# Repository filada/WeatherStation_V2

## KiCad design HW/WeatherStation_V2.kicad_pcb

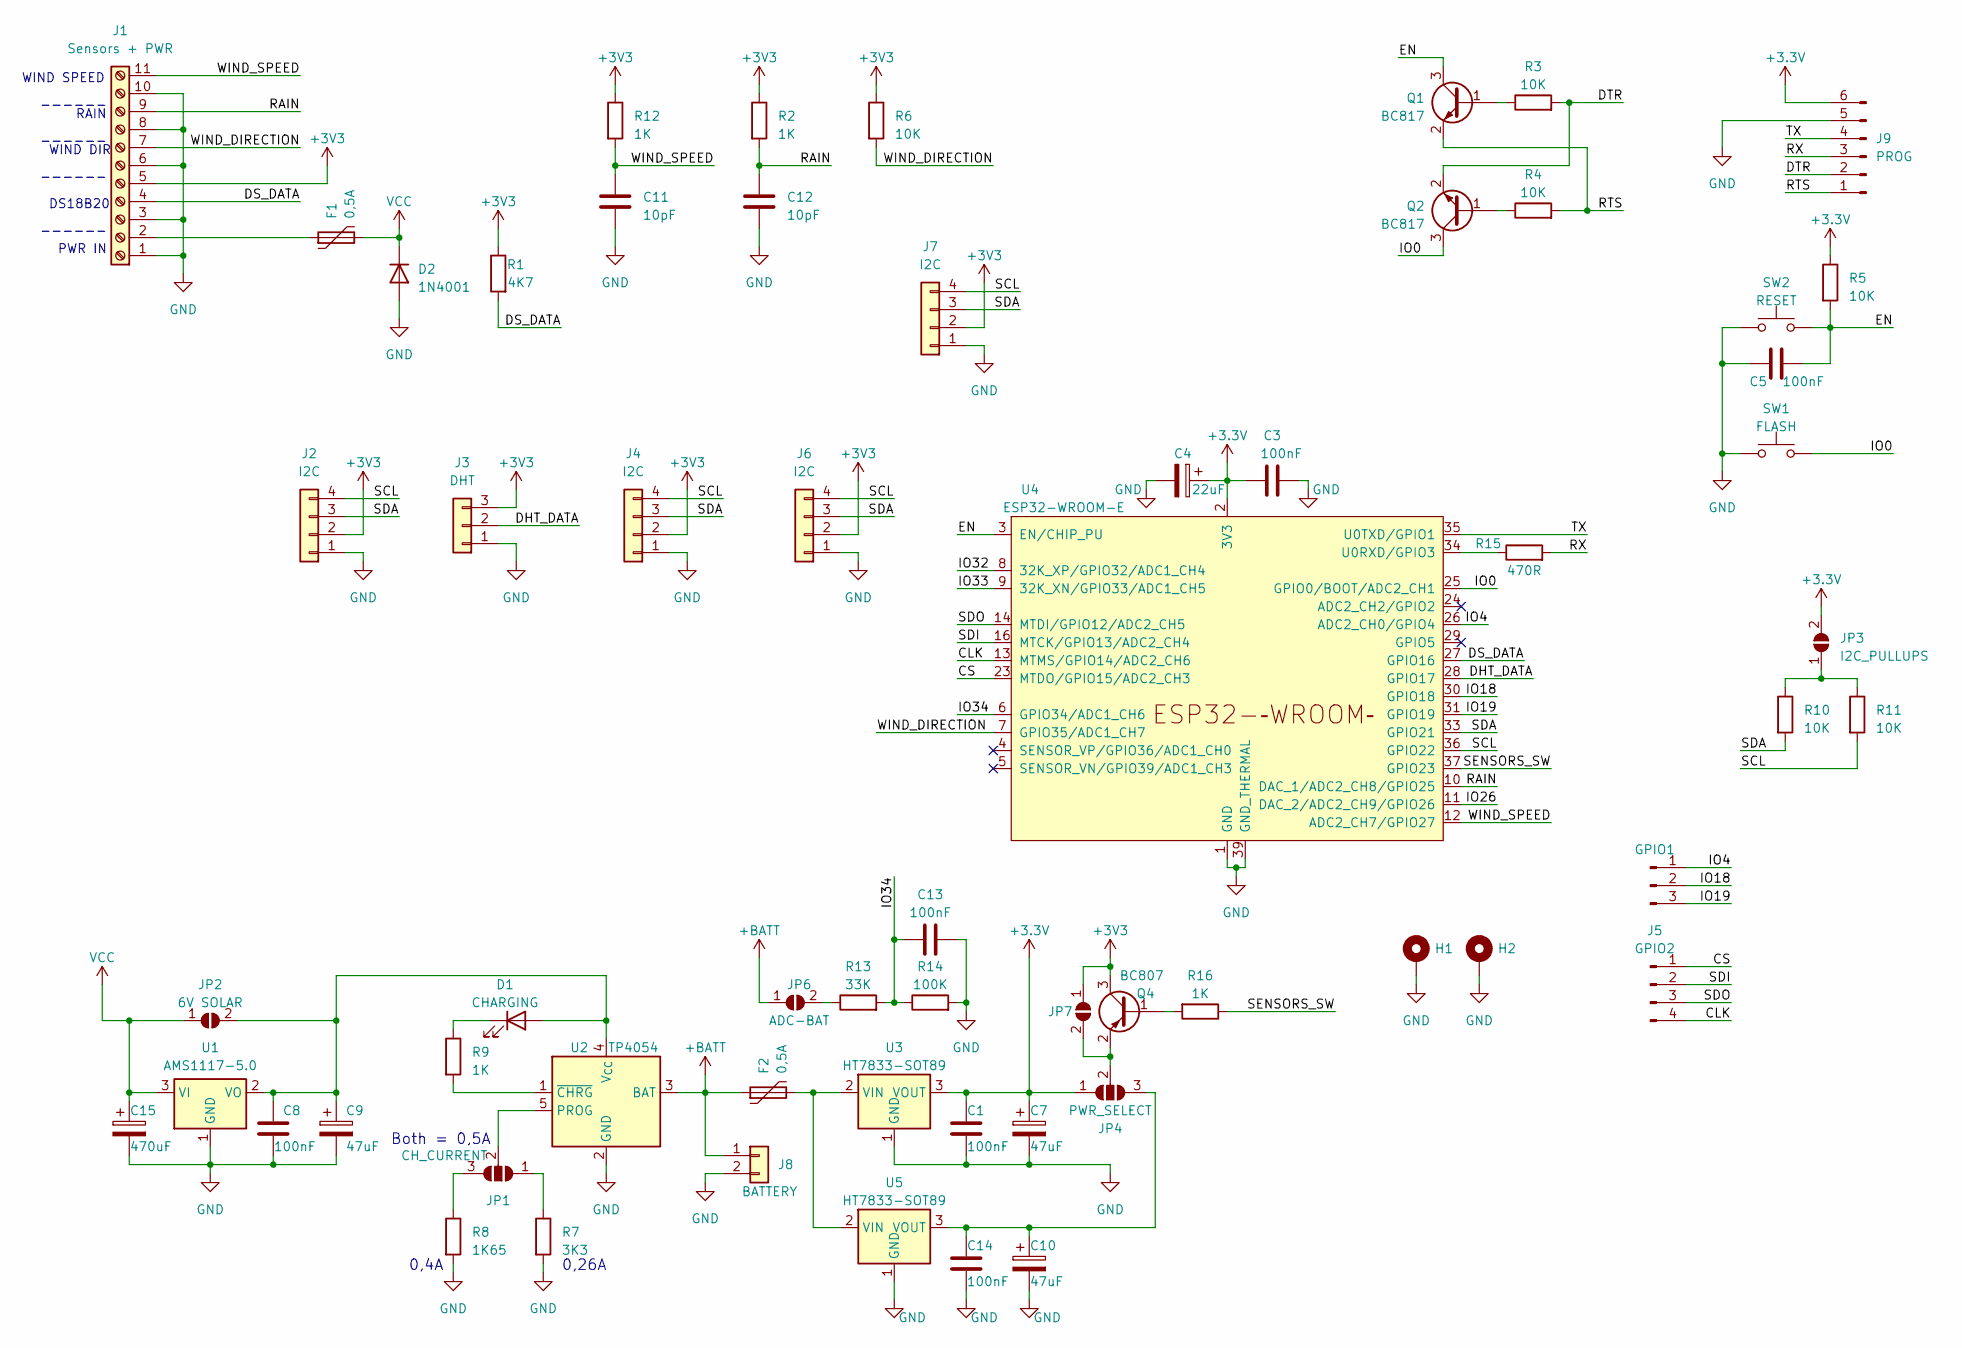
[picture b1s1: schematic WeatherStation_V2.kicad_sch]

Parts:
C1, C3, C5, C8, C13, C14: 100nF; C_0805_2012Metric_Pad1.18x1.45mm_HandSolder
C4: 22uF; C_0805_2012Metric_Pad1.18x1.45mm_HandSolder
C7, C9, C10: 47uF; CP_EIA-3216-18_Kemet-A_Pad1.58x1.35mm_HandSolder
C11, C12: 10pF; C_0805_2012Metric_Pad1.18x1.45mm_HandSolder
C15: 470uF; CP_Radial_D12.5mm_P7.50mm
D1: CHARGING; LED_1206_3216Metric_Pad1.42x1.75mm_HandSolder
D2: 1N4001; D_DO-41_SOD81_P10.16mm_Horizontal
F1, F2: 0,5A; Fuse_1206_3216Metric_Pad1.42x1.75mm_HandSolder
GPIO1: Conn_01x03_Pin; PinHeader_1x03_P2.54mm_Vertical
H1, H2: MountingHole_Pad; MountingHole_3.2mm_M3_DIN965_Pad
J1: Sensors + PWR; ScrewTerminal_1x11_P5.00mm_Vertical
J2, J4, J6, J7: I2C; JST_XH_B4B-XH-A_1x04_P2.50mm_Vertical
J3: DHT; JST_XH_B3B-XH-A_1x03_P2.50mm_Vertical
J5: GPIO2; PinHeader_1x04_P2.54mm_Vertical
J8: BATTERY; JST_XH_B2B-XH-A_1x02_P2.50mm_Vertical
J9: PROG; PinHeader_1x06_P2.54mm_Vertical
JP1: CH_CURRENT; SolderJumper-3_P1.3mm_Open_Pad1.0x1.5mm_NumberLabels
JP2, JP7: 6V SOLAR; SolderJumper-2_P1.3mm_Open_RoundedPad1.0x1.5mm
JP3: I2C_PULLUPS; SolderJumper-2_P1.3mm_Open_TrianglePad1.0x1.5mm
JP4: PWR_SELECT; SolderJumper-3_P1.3mm_Open_Pad1.0x1.5mm_NumberLabels
JP6: ADC-BAT; SolderJumper-2_P1.3mm_Open_TrianglePad1.0x1.5mm
Q1, Q2: BC817; SOT-23_Handsoldering
Q4: BC807; SOT-23_Handsoldering
R1: 4K7; R_0805_2012Metric_Pad1.20x1.40mm_HandSolder
R2, R9, R12, R16: 1K; R_0805_2012Metric_Pad1.20x1.40mm_HandSolder
R3, R4, R5, R6, R10, R11: 10K; R_0805_2012Metric_Pad1.20x1.40mm_HandSolder
R7: 3K3; R_0805_2012Metric_Pad1.20x1.40mm_HandSolder
R8: 1K65; R_0805_2012Metric_Pad1.20x1.40mm_HandSolder
R13: 33K; R_0805_2012Metric_Pad1.20x1.40mm_HandSolder
R14: 100K; R_0805_2012Metric_Pad1.20x1.40mm_HandSolder
R15: 470R; R_0805_2012Metric_Pad1.20x1.40mm_HandSolder
SW1: FLASH; SW_PUSH_SMALL
SW2: RESET; SW_PUSH_SMALL
U1: AMS1117-5.0; SOT-223-3_TabPin2
U2: TP4054; TSOT-23-5_HandSoldering
U3, U5: HT7833-SOT89; SOT-89-3_Handsoldering
U4: ESP32-WROOM-E; ESP32-WROOM-32E_HandSolder

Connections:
+3.3V: C1.1, C3.1, C4.1, C7.1, J9.6, JP3.2 (B), JP4.1 (A), R5.1, U3.3 (VOUT), U4.2 (3V3)
+3V3: J1.5, J2.2, J3.3, J4.2, J6.2, J7.2, JP7.1 (A), Q4.3 (C), R1.1, R2.1, R6.1, R12.1
+BATT: F2.1, J8.1, JP6.1 (A), U2.3 (BAT)
/CLK: J5.4, U4.13 (MTMS/GPIO14/ADC2_CH6)
/CS: J5.1, U4.23 (MTDO/GPIO15/ADC2_CH3)
/DHT_DATA: J3.2, U4.28 (GPIO17)
/DS_DATA: J1.4, R1.2, U4.27 (GPIO16)
/DTR: J9.2, Q2.2 (E), R3.2
/EN: C5.1, Q1.3 (C), R5.2, SW2.2, U4.3 (EN/CHIP_PU)
/IO0: Q2.3 (C), SW1.2, U4.25 (GPIO0/BOOT/ADC2_CH1)
/IO4: GPIO1.1, U4.26 (ADC2_CH0/GPIO4)
/IO18: GPIO1.2, U4.30 (GPIO18)
/IO19: GPIO1.3, U4.31 (GPIO19)
/IO26: U4.11 (DAC_2/ADC2_CH9/GPIO26)
/IO32: U4.8 (32K_XP/GPIO32/ADC1_CH4)
/IO33: U4.9 (32K_XN/GPIO33/ADC1_CH5)
/IO34: C13.1, R13.2, R14.1, U4.6 (GPIO34/ADC1_CH6)
/RAIN: C12.1, J1.9, R2.2, U4.10 (DAC_1/ADC2_CH8/GPIO25)
/RTS: J9.1, Q1.2 (E), R4.2
/RX: J9.3, R15.2
/SCL: J2.4, J4.4, J6.4, J7.4, R11.2, U4.36 (GPIO22)
/SDA: J2.3, J4.3, J6.3, J7.3, R10.2, U4.33 (GPIO21)
/SDI: J5.2, U4.16 (MTCK/GPIO13/ADC2_CH4)
/SDO: J5.3, U4.14 (MTDI/GPIO12/ADC2_CH5)
/SENSORS_SW: R16.1, U4.37 (GPIO23)
/TX: J9.4, U4.35 (U0TXD/GPIO1)
/WIND_DIRECTION: J1.7, R6.2, U4.7 (GPIO35/ADC1_CH7)
/WIND_SPEED: C11.1, J1.11, R12.2, U4.12 (ADC2_CH7/GPIO27)
GND: C1.2, C3.2, C4.2, C5.2, C7.2, C8.2, C9.2, C10.2, C11.2, C12.2, C13.2, C14.2, C15.2, D2.2 (A), H1.1, H2.1, J1.1, J1.3, J1.6, J1.8, J1.10, J2.1, J3.1, J4.1, J6.1, J7.1, J8.2, J9.5, R7.2, R8.2, R14.2, SW1.1, SW2.1, U1.1 (GND), U2.2 (GND), U3.1 (GND), U4.1 (GND), U4.15 (GND), U4.38 (GND), U4.39 (GND_THERMAL), U5.1 (GND)
unnamed: C8.1, C9.1, D1.2 (A), JP2.2 (B), U1.2 (VO), U2.4 (V_{CC})
unnamed: D1.1 (K), R9.1
unnamed: F1.1, J1.2
unnamed: JP1.1 (A), R7.1
unnamed: JP1.3 (B), R8.1
unnamed: JP1.2 (C), U2.5 (PROG)
unnamed: JP3.1 (A), R10.1, R11.1
unnamed: C10.1, C14.1, JP4.3 (B), U5.3 (VOUT)
unnamed: JP4.2 (C), JP7.2 (B), Q4.2 (E)
unnamed: JP6.2 (B), R13.1
unnamed: Q1.1 (B), R3.1
unnamed: Q2.1 (B), R4.1
unnamed: Q4.1 (B), R16.2
unnamed: R9.2, U2.1 (~CHRG)
unnamed: F2.2, U3.2 (VIN), U5.2 (VIN)
unnamed: R15.1, U4.34 (U0RXD/GPIO3)
VCC: C15.1, D2.1 (K), F1.2, JP2.1 (A), U1.3 (VI)

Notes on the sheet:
WIND SPEED
------
PWR IN
0,26A
RAIN
Both = 0,5A
DS18B20
WIND DIR
0,4A

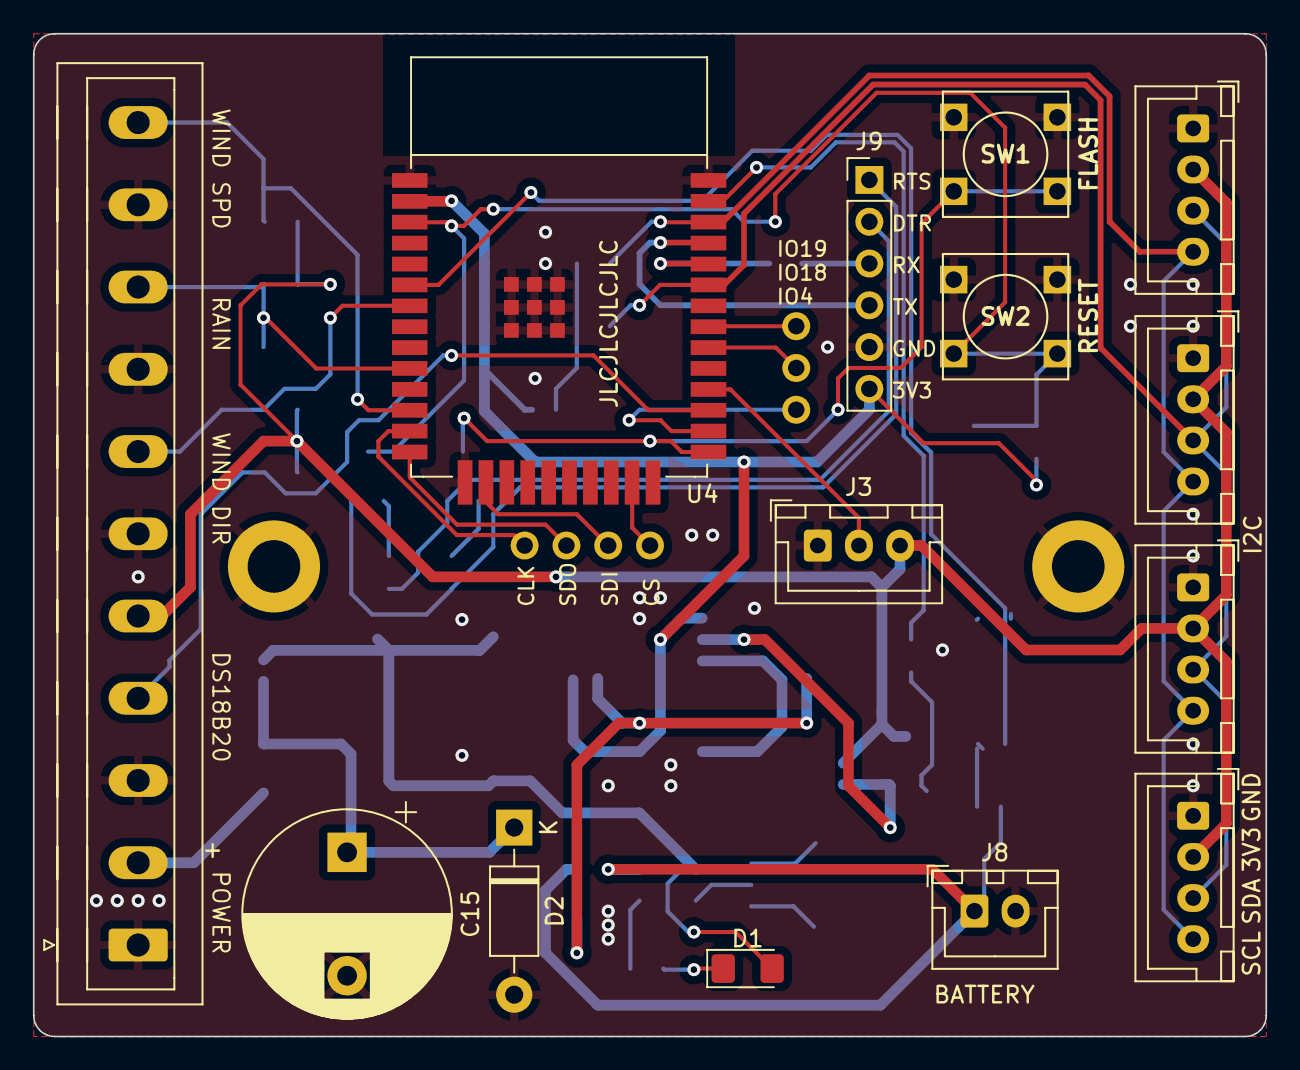
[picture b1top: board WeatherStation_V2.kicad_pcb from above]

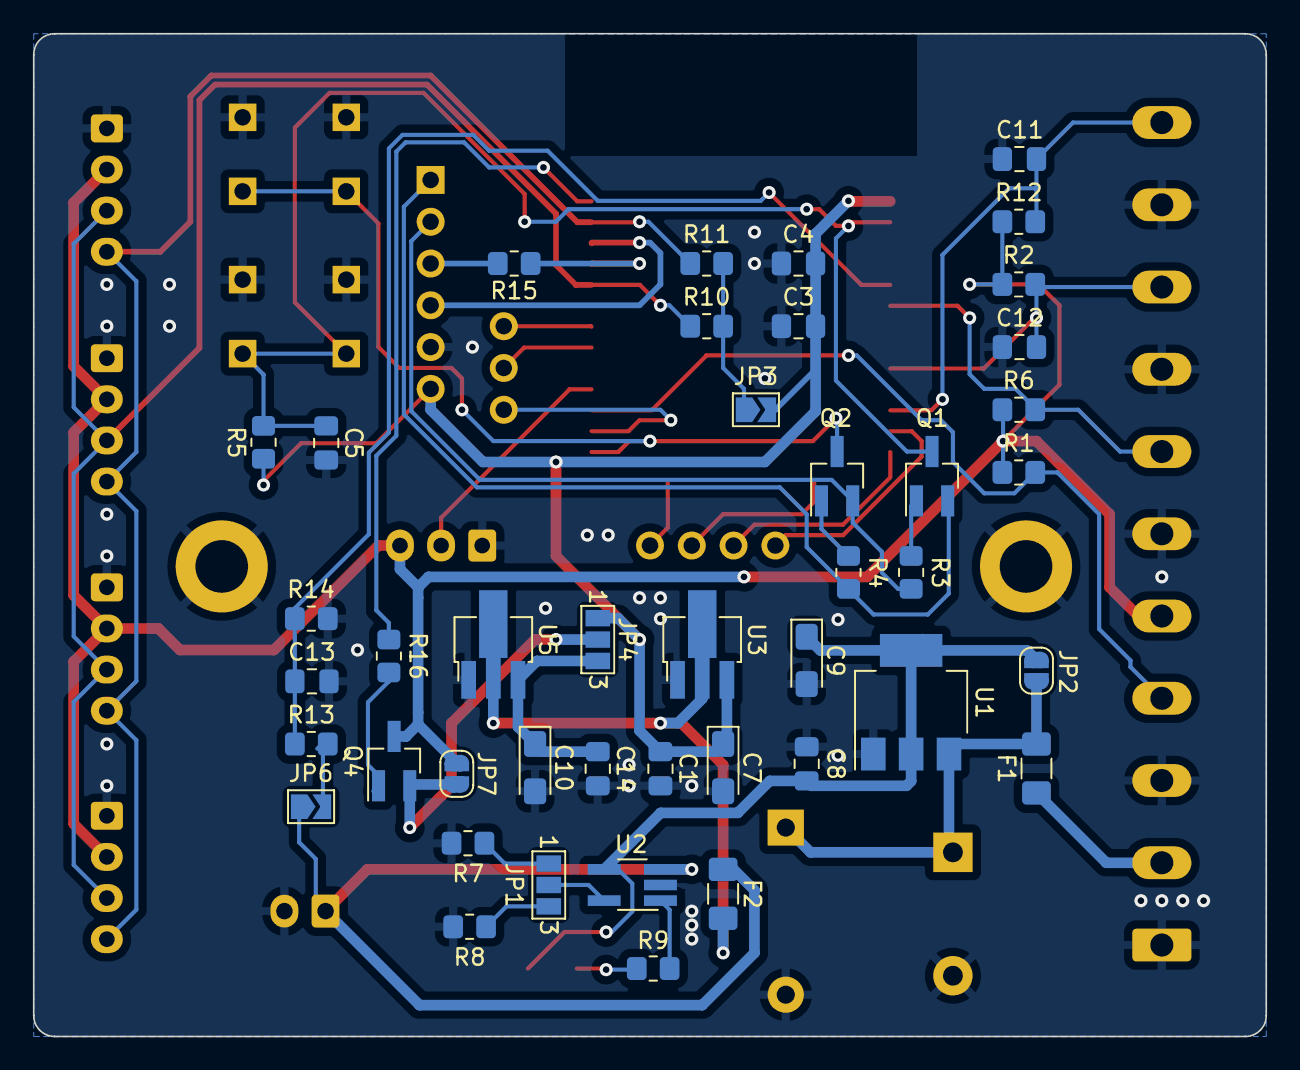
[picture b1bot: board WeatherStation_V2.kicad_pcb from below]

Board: 2 copper layers, 74.9 x 61.0 mm, 61 parts (43 on the bottom side), 43 nets.

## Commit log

2023-12-10 first version of PCB
2023-12-10 PCB files moved to PCB folder
2023-12-10 folder PCB renamed to HW
2023-12-15 Updated PCB - DRC OK
    DRC without any error;
    some small improvements in scheme
2023-12-16 small improvements
2023-12-22 added keepout area
    Updated antenna area - added keepout area
    Updated text on Silkscreen layer
2024-01-30 3 pin battery connector updated to 2 pin
2024-02-17 Updated design rules
    Updated for production in JLCPCB
2024-02-20 Fixed copper layer
2024-07-17 Create WeatherStation_V2_SCH.pdf
    Added PDF schematic
2025-05-08 First FW
    Added PCB Assembly PDF, organized folders, added basic firmware
2025-05-08 FW with DHT22 support
2025-05-10 code updated
